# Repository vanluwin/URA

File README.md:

# URA
# Projeto um Robô Por Aluno

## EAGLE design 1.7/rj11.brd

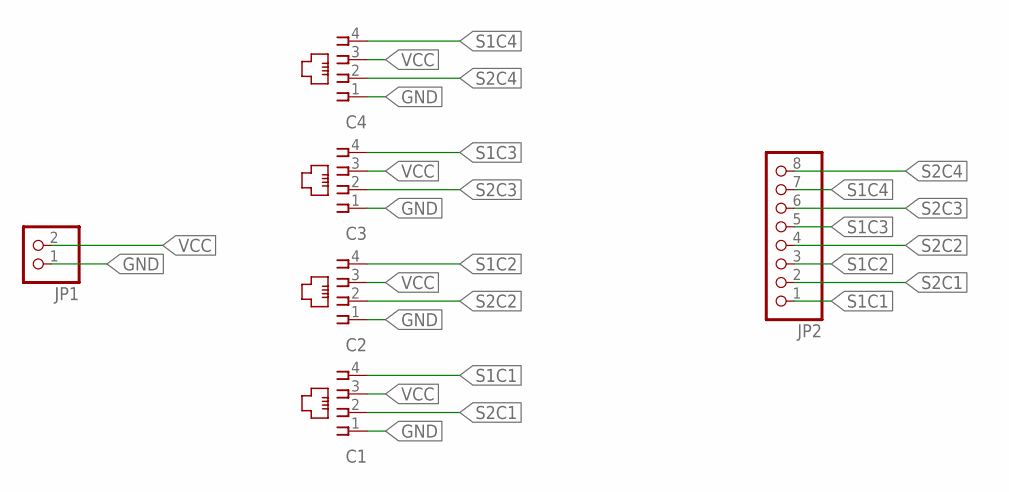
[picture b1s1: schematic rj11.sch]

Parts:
C1, C2, C3, C4: 14867
JP1: PINHD-1X2; 1X02
JP2: PINHD-1X8; 1X08

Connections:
GND: C1.1, C2.1, C3.1, C4.1, JP1.1
S1C1: C1.4, JP2.1
S1C2: C2.4, JP2.3
S1C3: C3.4, JP2.5
S1C4: C4.4, JP2.7
S2C1: C1.2, JP2.2
S2C2: C2.2, JP2.4
S2C3: C3.2, JP2.6
S2C4: C4.2, JP2.8
VCC: C1.3, C2.3, C3.3, C4.3, JP1.2

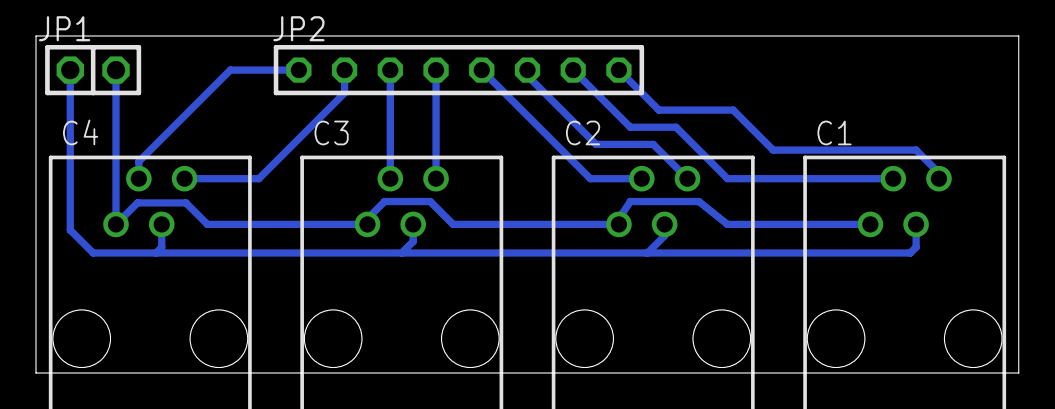
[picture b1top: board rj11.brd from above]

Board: 2 copper layers, 54.6 x 18.7 mm, 6 parts (0 on the bottom side), 10 nets.

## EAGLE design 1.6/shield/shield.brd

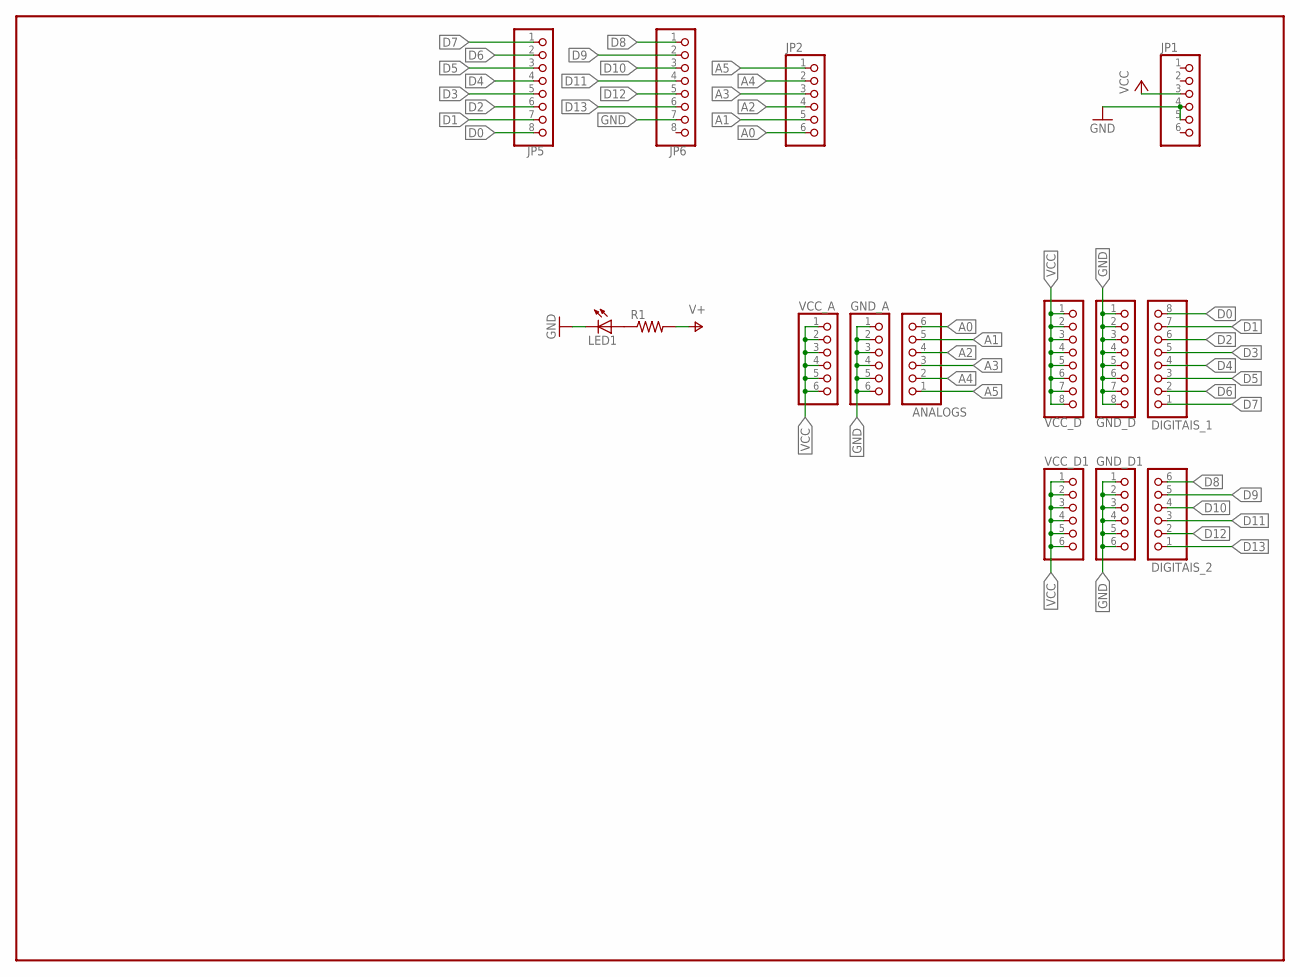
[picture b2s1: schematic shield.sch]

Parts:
ANALOGS: PINHD-1X6; 1X06
DIGITAIS_1: PINHD-1X8; 1X08
DIGITAIS_2: PINHD-1X6; 1X06
GND_A: PINHD-1X6; 1X06
GND_D: PINHD-1X8; 1X08
GND_D1: PINHD-1X6; 1X06
JP1, JP2: PINHD-1X6; 1X06
JP5, JP6: PINHD-1X8; 1X08
LED1: LED3MM
R1: R-US_0207/10; 0207/10
VCC_A: PINHD-1X6; 1X06
VCC_D: PINHD-1X8; 1X08
VCC_D1: PINHD-1X6; 1X06

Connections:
A0: ANALOGS.6, JP2.6
A1: ANALOGS.5, JP2.5
A2: ANALOGS.4, JP2.4
A3: ANALOGS.3, JP2.3
A4: ANALOGS.2, JP2.2
A5: ANALOGS.1, JP2.1
D0: DIGITAIS_1.8, JP5.8
D1: DIGITAIS_1.7, JP5.7
D2: DIGITAIS_1.6, JP5.6
D3: DIGITAIS_1.5, JP5.5
D4: DIGITAIS_1.4, JP5.4
D5: DIGITAIS_1.3, JP5.3
D6: DIGITAIS_1.2, JP5.2
D7: DIGITAIS_1.1, JP5.1
D8: DIGITAIS_2.6, JP6.1
D9: DIGITAIS_2.5, JP6.2
D10: DIGITAIS_2.4, JP6.3
D11: DIGITAIS_2.3, JP6.4
D12: DIGITAIS_2.2, JP6.5
D13: DIGITAIS_2.1, JP6.6
GND: GND_A.1, GND_A.2, GND_A.3, GND_A.4, GND_A.5, GND_A.6, GND_D.1, GND_D.2, GND_D.3, GND_D.4, GND_D.5, GND_D.6, GND_D.7, GND_D.8, GND_D1.1, GND_D1.2, GND_D1.3, GND_D1.4, GND_D1.5, GND_D1.6, JP1.4, JP1.5, JP6.7, LED1.K (C)
unnamed: LED1.A, R1.1
VCC: JP1.3, R1.2, VCC_A.1, VCC_A.2, VCC_A.3, VCC_A.4, VCC_A.5, VCC_A.6, VCC_D.1, VCC_D.2, VCC_D.3, VCC_D.4, VCC_D.5, VCC_D.6, VCC_D.7, VCC_D.8, VCC_D1.1, VCC_D1.2, VCC_D1.3, VCC_D1.4, VCC_D1.5, VCC_D1.6

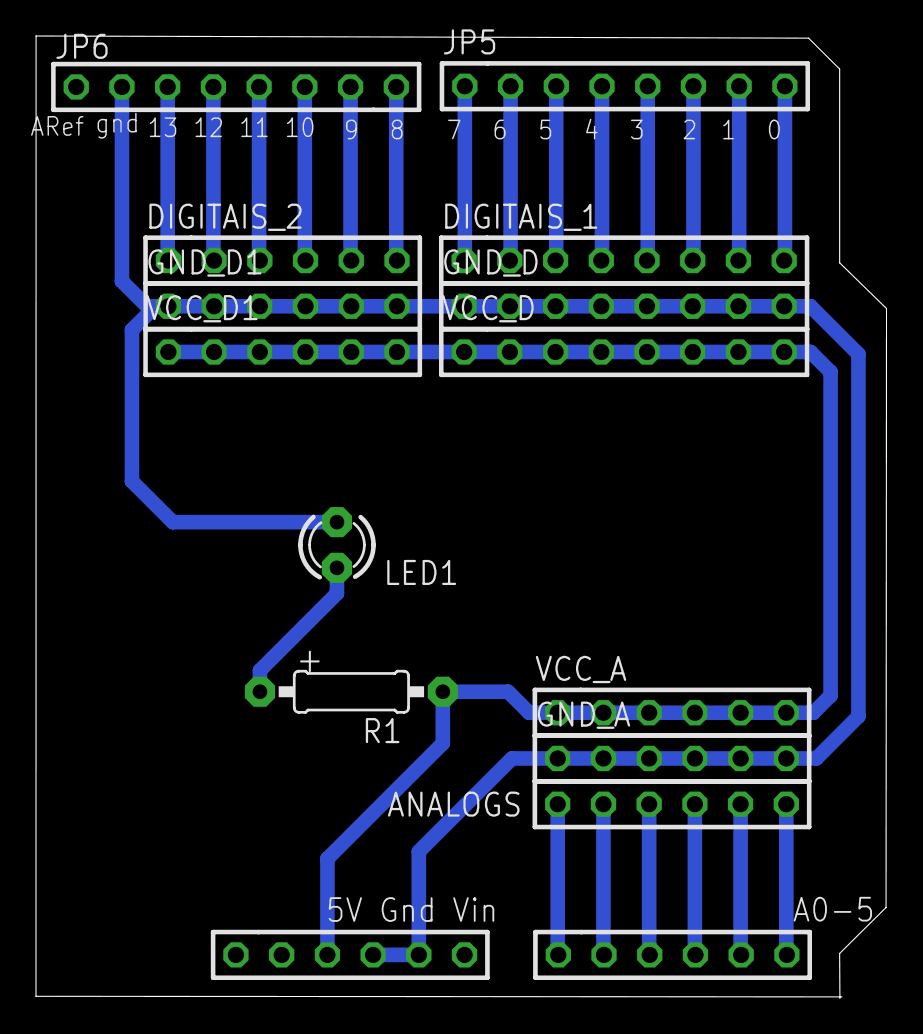
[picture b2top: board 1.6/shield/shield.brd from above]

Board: 2 copper layers, 47.3 x 53.5 mm, 15 parts (0 on the bottom side), 23 nets.

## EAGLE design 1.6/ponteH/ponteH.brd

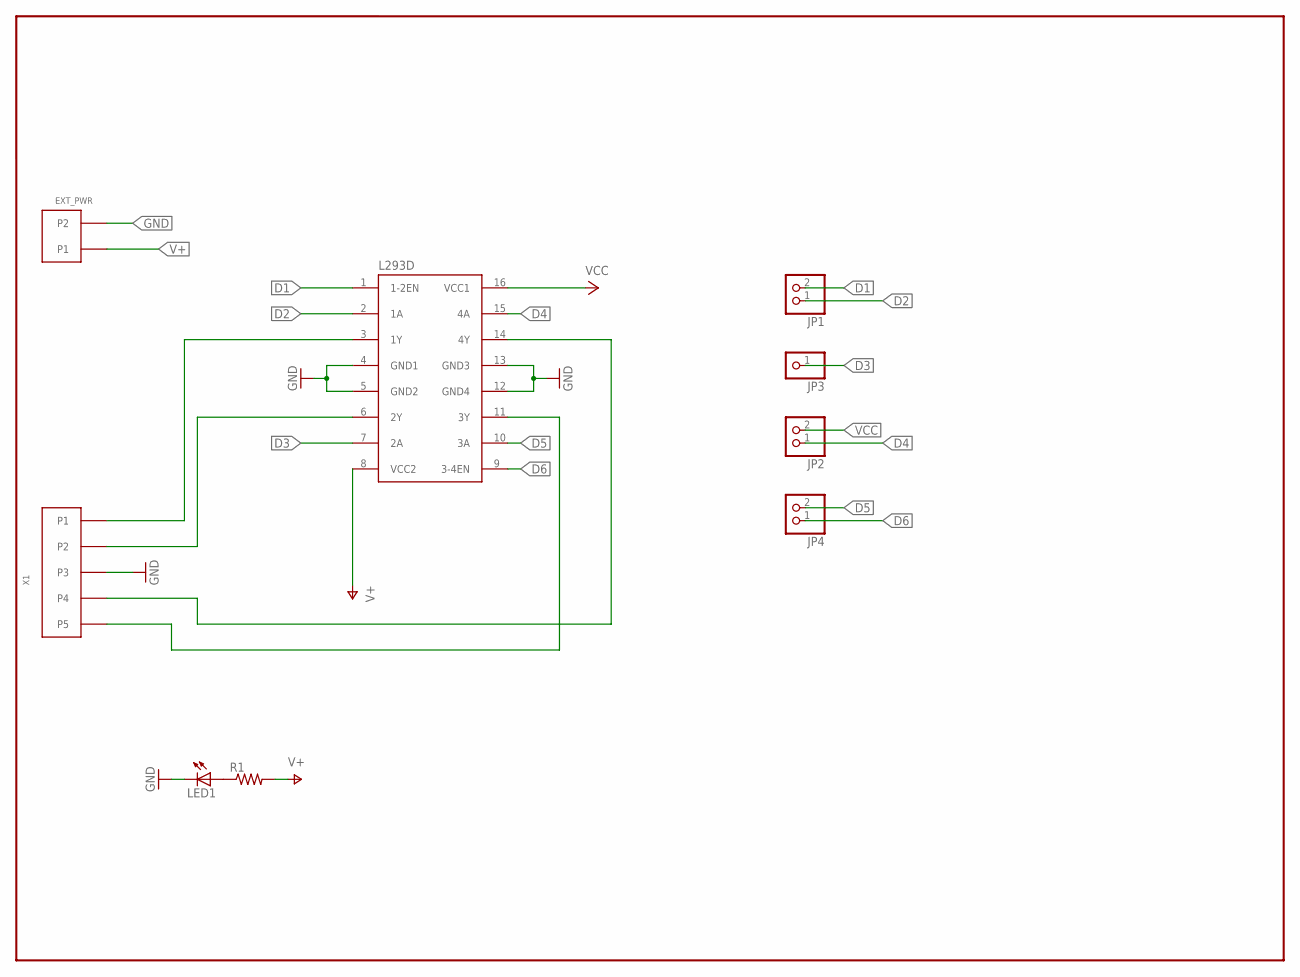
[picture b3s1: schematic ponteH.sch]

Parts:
EXT_PWR: PINHEAD; TERMBLOCK508
JP1, JP2, JP4: PINHD-1X2; 1X02
JP3: PINHD-1X1; 1X01
L293D: L293E; DIL16
LED1: LED3MM
R1: R-US_0207/10; 0207/10
X1: TERM5; TERM1X5

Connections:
D1: JP1.2, L293D.1 (1-2EN)
D2: JP1.1, L293D.2 (1A)
D3: JP3.1, L293D.7 (2A)
D4: JP2.1, L293D.15 (4A)
D5: JP4.2, L293D.10 (3A)
D6: JP4.1, L293D.9 (3-4EN)
GND: EXT_PWR.P$4 (P2), L293D.4 (GND1), L293D.5 (GND2), L293D.12 (GND4), L293D.13 (GND3), LED1.K (C), X1.P3
unnamed: L293D.3 (1Y), X1.P1
unnamed: L293D.6 (2Y), X1.P2
unnamed: L293D.11 (3Y), X1.P5
unnamed: L293D.14 (4Y), X1.P4
unnamed: LED1.A, R1.1
V+: EXT_PWR.P$3 (P1), L293D.8 (VCC2), R1.2
VCC: JP2.2, L293D.16 (VCC1)

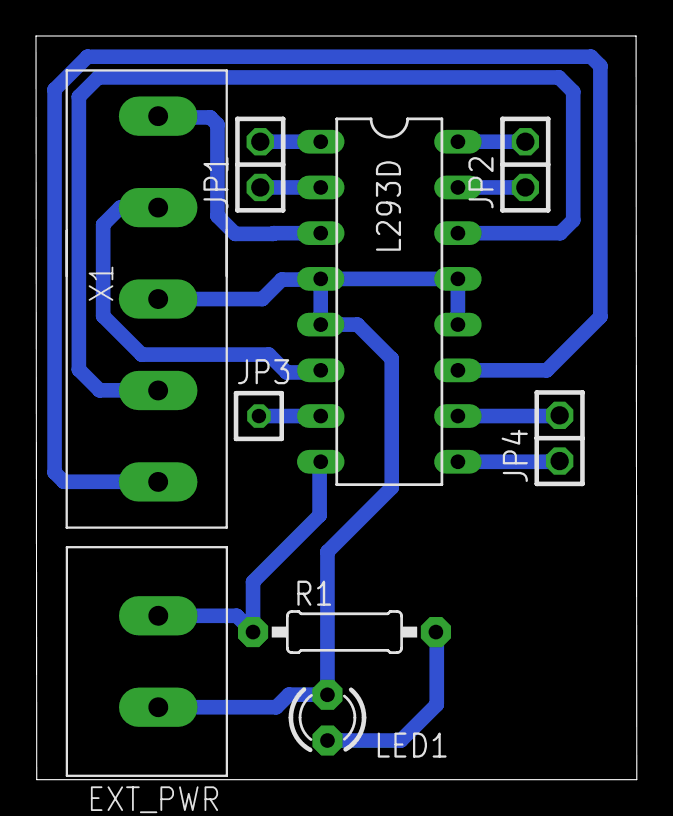
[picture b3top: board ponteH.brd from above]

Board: 2 copper layers, 33.4 x 41.3 mm, 9 parts (0 on the bottom side), 14 nets.

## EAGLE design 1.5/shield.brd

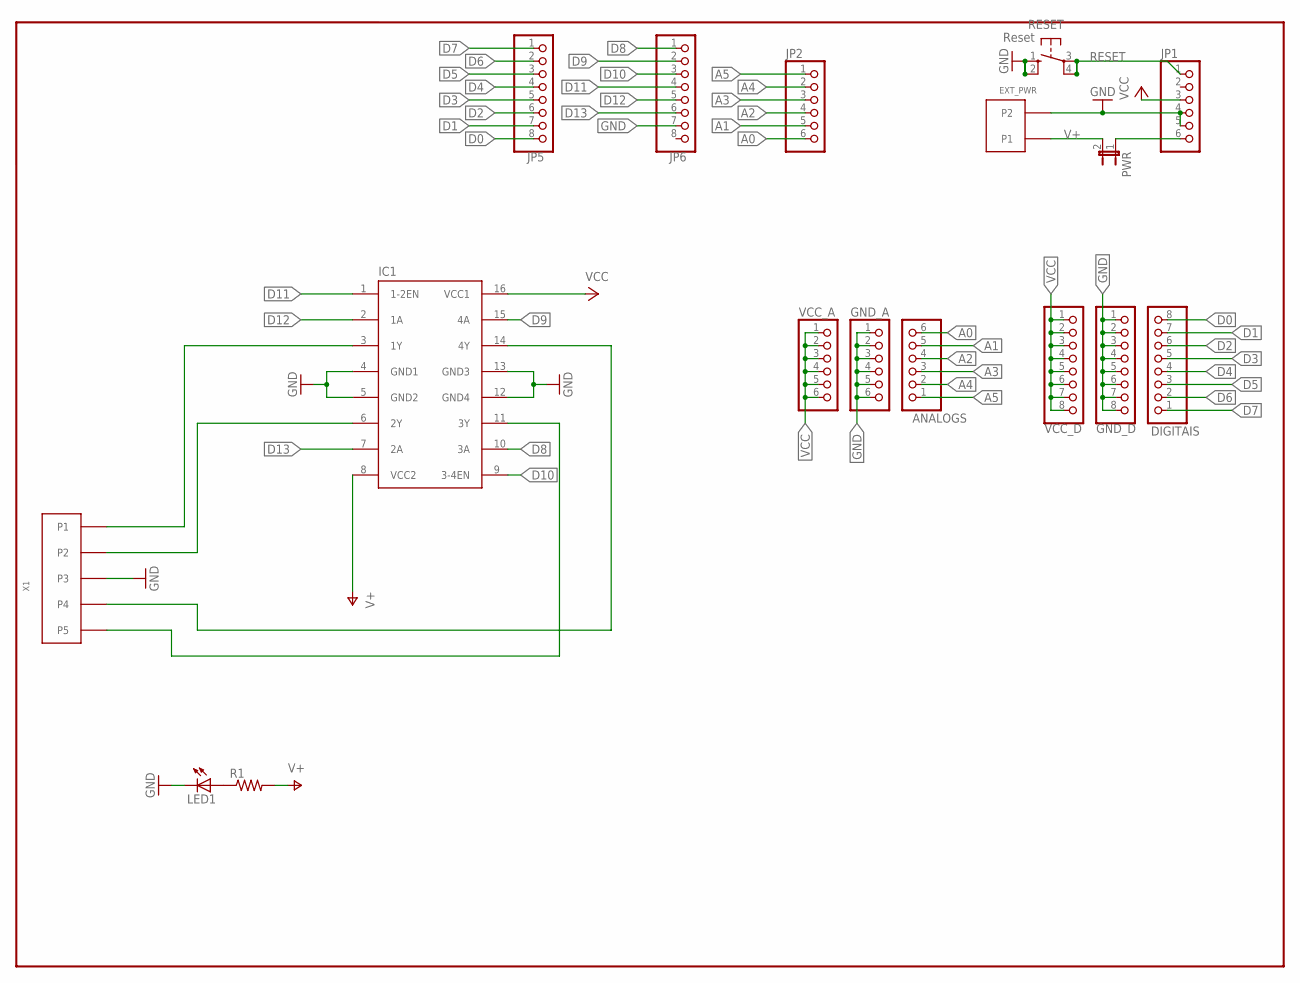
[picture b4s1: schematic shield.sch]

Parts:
ANALOGS: PINHD-1X6; 1X06
DIGITAIS: PINHD-1X8; 1X08
EXT_PWR: PINHEAD; TERMBLOCK508
GND_A: PINHD-1X6; 1X06
GND_D: PINHD-1X8; 1X08
IC1: L293E; DIL16
JP1, JP2: PINHD-1X6; 1X06
JP5, JP6: PINHD-1X8; 1X08
LED1: LED3MM
PWR: JP1E; JP1
R1: R-US_0207/10; 0207/10
RESET: Reset; B3F-10XX
VCC_A: PINHD-1X6; 1X06
VCC_D: PINHD-1X8; 1X08
X1: TERM5; TERM1X5

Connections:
9V: JP1.6, PWR.1
A0: ANALOGS.6, JP2.6
A1: ANALOGS.5, JP2.5
A2: ANALOGS.4, JP2.4
A3: ANALOGS.3, JP2.3
A4: ANALOGS.2, JP2.2
A5: ANALOGS.1, JP2.1
D0: DIGITAIS.8, JP5.8
D1: DIGITAIS.7, JP5.7
D2: DIGITAIS.6, JP5.6
D3: DIGITAIS.5, JP5.5
D4: DIGITAIS.4, JP5.4
D5: DIGITAIS.3, JP5.3
D6: DIGITAIS.2, JP5.2
D7: DIGITAIS.1, JP5.1
D8: IC1.10 (3A), JP6.1
D9: IC1.15 (4A), JP6.2
D10: IC1.9 (3-4EN), JP6.3
D11: IC1.1 (1-2EN), JP6.4
D12: IC1.2 (1A), JP6.5
D13: IC1.7 (2A), JP6.6
GND: EXT_PWR.P$4 (P2), GND_A.1, GND_A.2, GND_A.3, GND_A.4, GND_A.5, GND_A.6, GND_D.1, GND_D.2, GND_D.3, GND_D.4, GND_D.5, GND_D.6, GND_D.7, GND_D.8, IC1.4 (GND1), IC1.5 (GND2), IC1.12 (GND4), IC1.13 (GND3), JP1.4, JP1.5, JP6.7, LED1.K (C), RESET.1 (S), RESET.2 (S1), X1.P3
unnamed: IC1.3 (1Y), X1.P1
unnamed: IC1.6 (2Y), X1.P2
unnamed: IC1.11 (3Y), X1.P5
unnamed: IC1.14 (4Y), X1.P4
unnamed: LED1.A, R1.1
RESET: JP1.1, RESET.3, RESET.4 (P1)
V+: EXT_PWR.P$3 (P1), IC1.8 (VCC2), PWR.2, R1.2
VCC: IC1.16 (VCC1), JP1.3, VCC_A.1, VCC_A.2, VCC_A.3, VCC_A.4, VCC_A.5, VCC_A.6, VCC_D.1, VCC_D.2, VCC_D.3, VCC_D.4, VCC_D.5, VCC_D.6, VCC_D.7, VCC_D.8

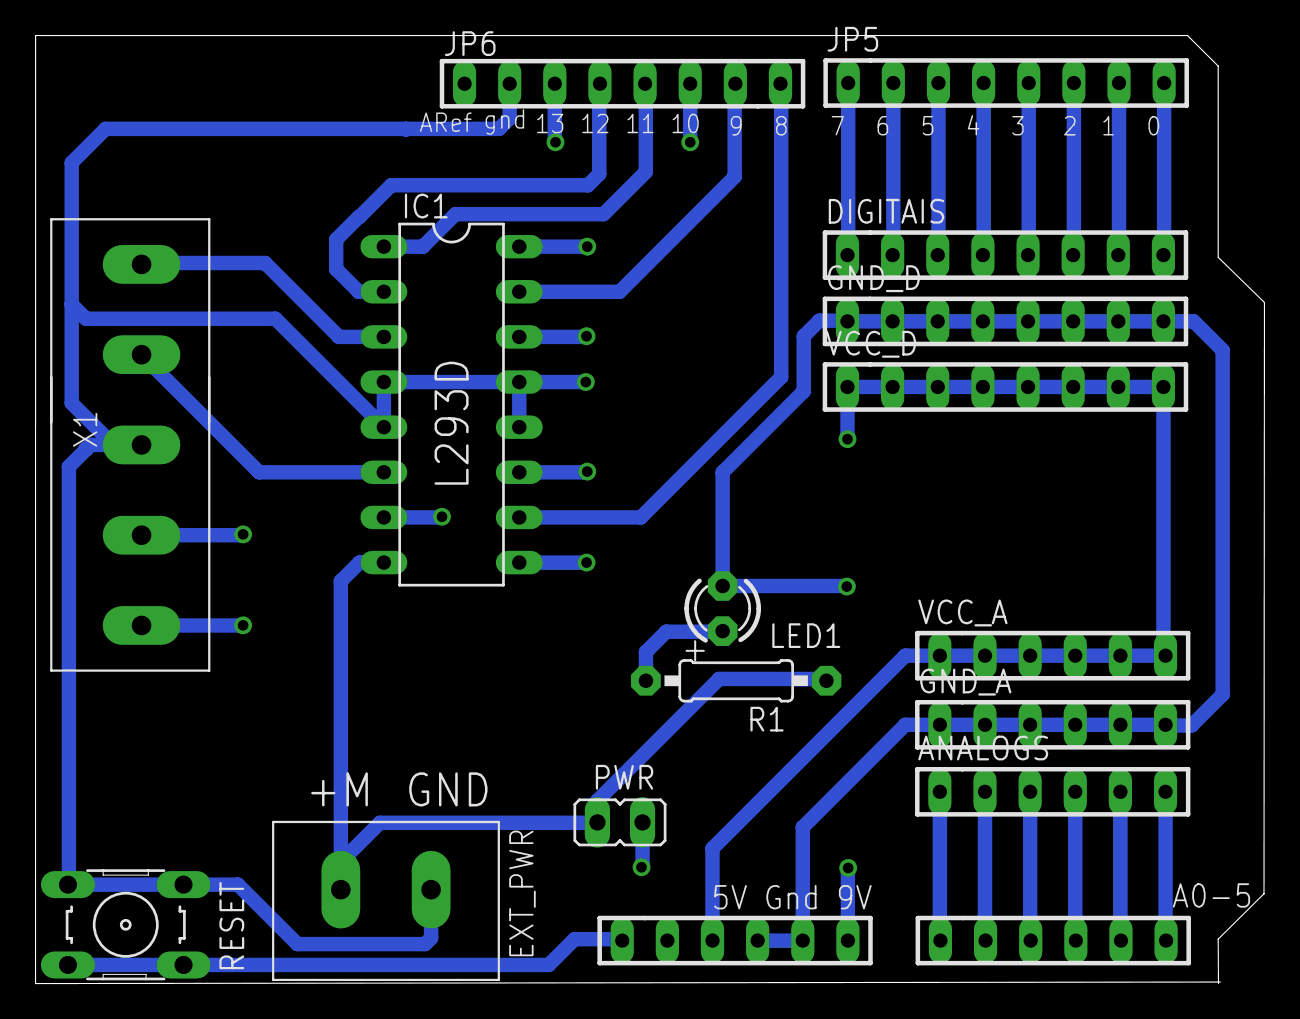
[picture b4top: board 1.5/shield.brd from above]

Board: 2 copper layers, 69.2 x 53.4 mm, 17 parts (0 on the bottom side), 30 nets.

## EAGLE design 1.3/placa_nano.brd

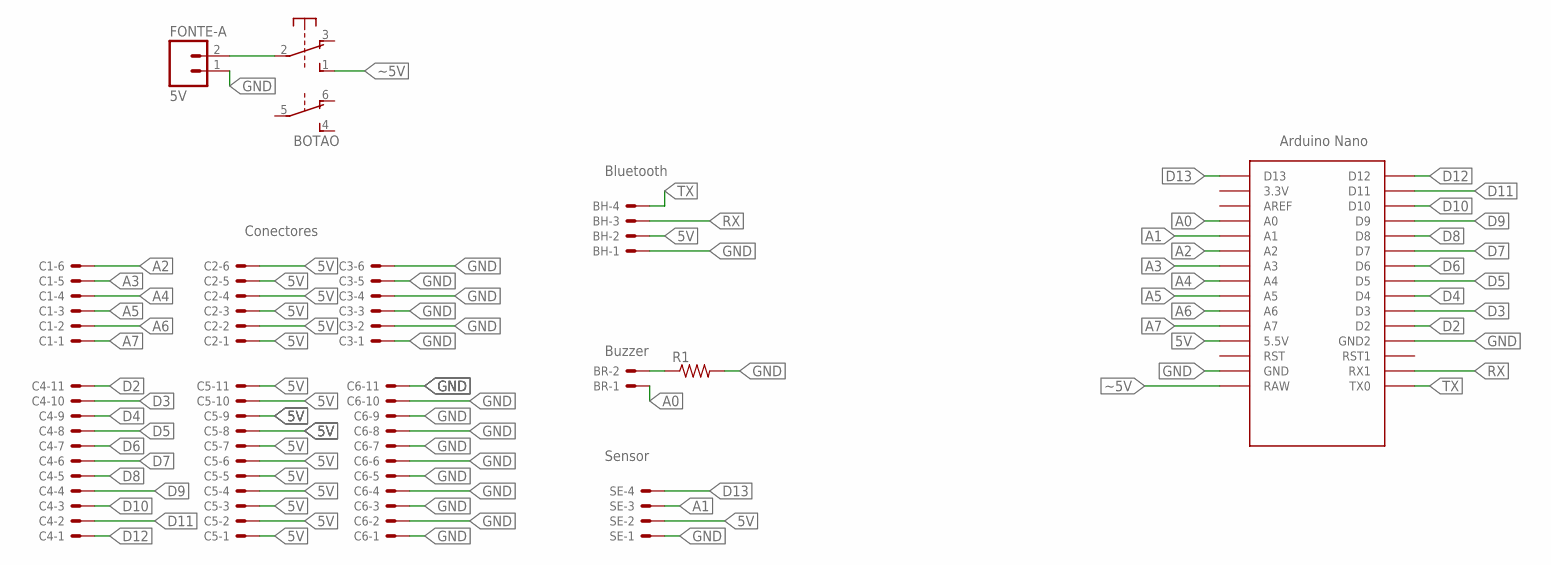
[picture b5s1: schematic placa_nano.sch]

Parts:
BH: 22-23-2041
BOTAO: 9077-2
BR: 22-23-2021
C1, C2, C3: 22-23-2061
C4, C5, C6: 22-23-2111
FONTE-A: 5V; 02P
R1: R-US_0207/10; 0207/10
SE: 22-23-2041
U$1: NANO

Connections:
5V: BH.2, C2.1, C2.2, C2.3, C2.4, C2.5, C2.6, C5.1, C5.2, C5.3, C5.4, C5.5, C5.6, C5.7, C5.8, C5.9, C5.10, C5.11, SE.2, U$1.5V (5.5V)
A0: BR.1, U$1.A0
A1: SE.3, U$1.A1
A2: C1.6, U$1.A2
A3: C1.5, U$1.A3
A4: C1.4, U$1.A4
A5: C1.3, U$1.A5
A6: C1.2, U$1.A6
A7: C1.1, U$1.A7
D2: C4.11, U$1.D2
D3: C4.10, U$1.D3
D4: C4.9, U$1.D4
D5: C4.8, U$1.D5
D6: C4.7, U$1.D6
D7: C4.6, U$1.D7
D8: C4.5, U$1.D8
D9: C4.4, U$1.D9
D10: C4.3, U$1.D10
D11: C4.2, U$1.D11
D12: C4.1, U$1.D12
D13: SE.4, U$1.D13
GND: BH.1, C3.1, C3.2, C3.3, C3.4, C3.5, C3.6, C6.1, C6.2, C6.3, C6.4, C6.5, C6.6, C6.7, C6.8, C6.9, C6.10, C6.11, FONTE-A.1, R1.2, SE.1, U$1.GND, U$1.GND1 (GND2)
unnamed: BR.2, R1.1
RX: BH.3, U$1.RX1
TX: BH.4, U$1.TX0
~5V: BOTAO.1 (S), BOTAO.2, FONTE-A.2, U$1.RAW

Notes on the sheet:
Bluetooth
Buzzer
Sensor
Conectores

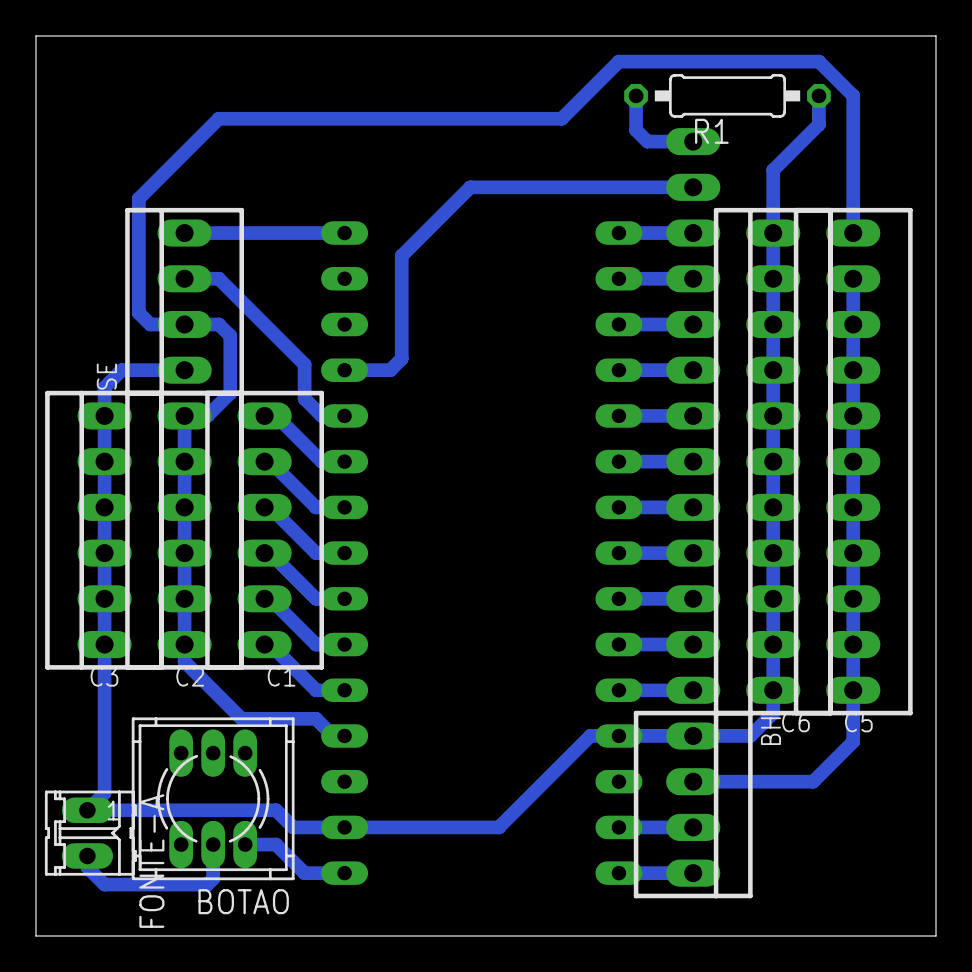
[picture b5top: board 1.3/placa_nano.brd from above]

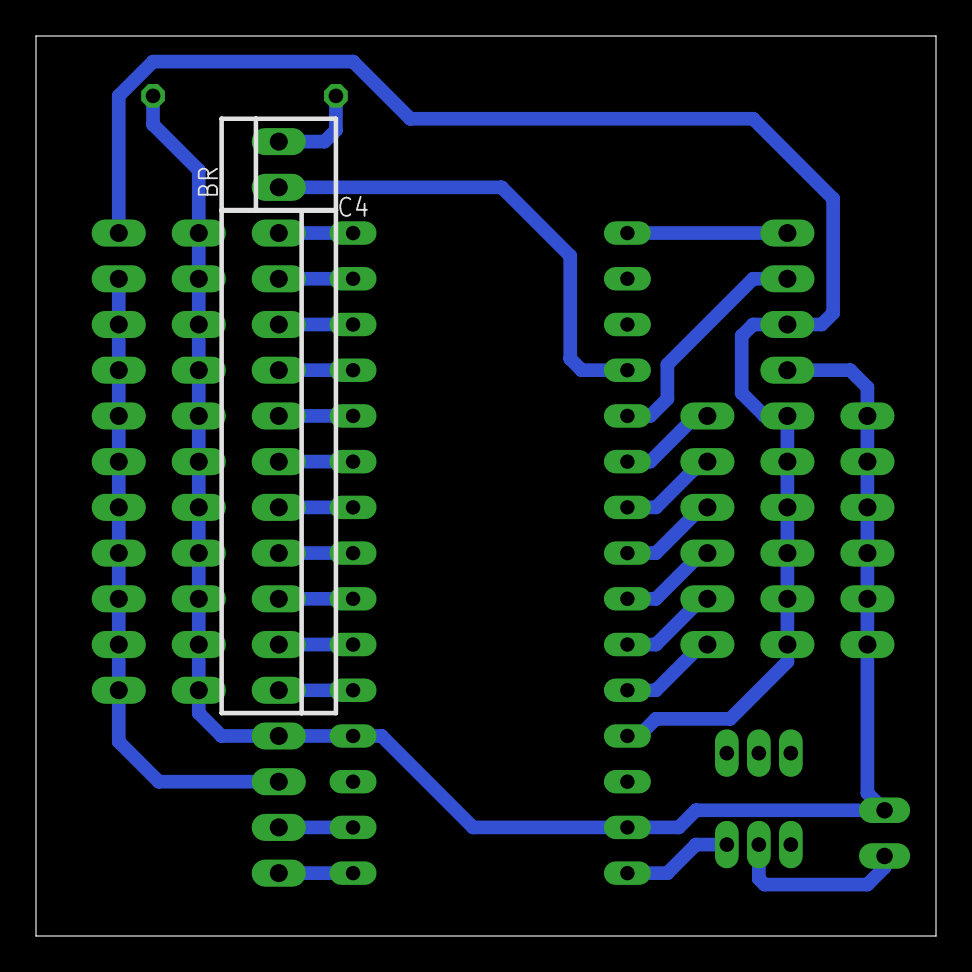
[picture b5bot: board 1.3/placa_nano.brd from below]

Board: 2 copper layers, 50.0 x 50.0 mm, 13 parts (2 on the bottom side), 26 nets.

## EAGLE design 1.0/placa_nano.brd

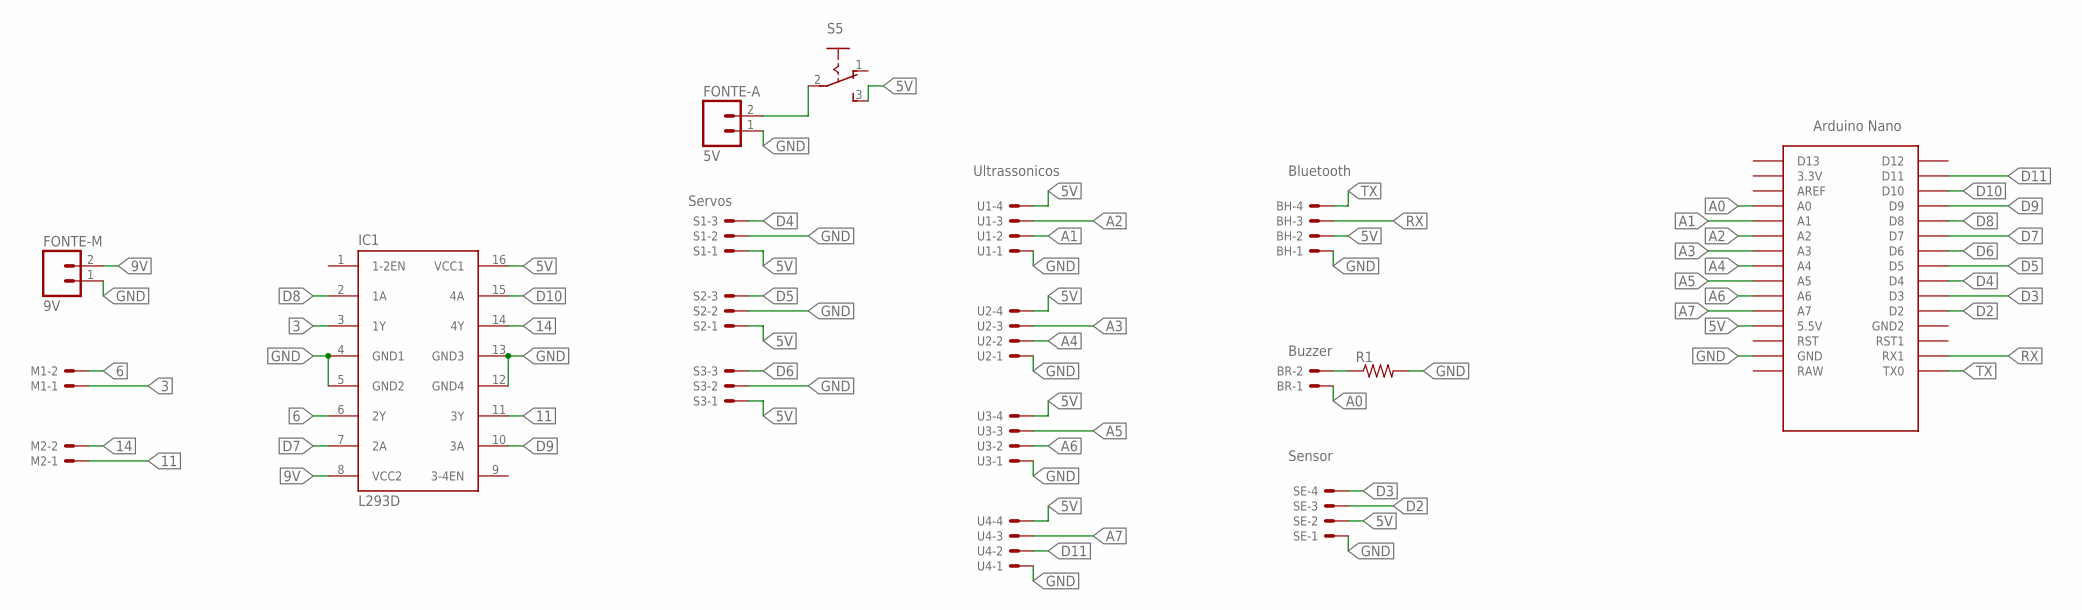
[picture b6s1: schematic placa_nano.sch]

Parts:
BH: 22-23-2041
BR: 22-23-2021
FONTE-A: 5V; 02P
FONTE-M: 9V; 02P
IC1: L293D; DIL16
M1, M2: 22-23-2021
R1: R-US_0207/10; 0207/10
S1, S2, S3: 22-23-2031
S5: 255SB
SE: 22-23-2041
U1, U2, U3, U4: 22-23-2041
U$1: NANO

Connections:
3: IC1.3 (1Y), M1.1
5V: BH.2, FONTE-A.2, IC1.16 (VCC1), S1.1, S2.1, S3.1, S5.2, S5.3 (S), SE.2, U1.4, U2.4, U3.4, U4.4, U$1.5V (5.5V)
6: IC1.6 (2Y), M1.2
9V: FONTE-M.2, IC1.8 (VCC2)
11: IC1.11 (3Y), M2.1
14: IC1.14 (4Y), M2.2
A0: BR.1, U$1.A0
A1: U1.2, U$1.A1
A2: U1.3, U$1.A2
A3: U2.3, U$1.A3
A4: U2.2, U$1.A4
A5: U3.3, U$1.A5
A6: U3.2, U$1.A6
A7: U4.3, U$1.A7
D2: SE.3, U$1.D2
D3: SE.4, U$1.D3
D4: S1.3, U$1.D4
D5: S2.3, U$1.D5
D6: S3.3, U$1.D6
D7: IC1.7 (2A), U$1.D7
D8: IC1.2 (1A), U$1.D8
D9: IC1.10 (3A), U$1.D9
D10: IC1.15 (4A), U$1.D10
D11: U4.2, U$1.D11
GND: BH.1, FONTE-A.1, FONTE-M.1, IC1.4 (GND1), IC1.5 (GND2), IC1.12 (GND4), IC1.13 (GND3), R1.2, S1.2, S2.2, S3.2, SE.1, U1.1, U2.1, U3.1, U4.1, U$1.GND
unnamed: BR.2, R1.1
RX: BH.3, U$1.RX1
TX: BH.4, U$1.TX0

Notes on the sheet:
Servos
Ultrassonicos
Bluetooth
Buzzer
Sensor

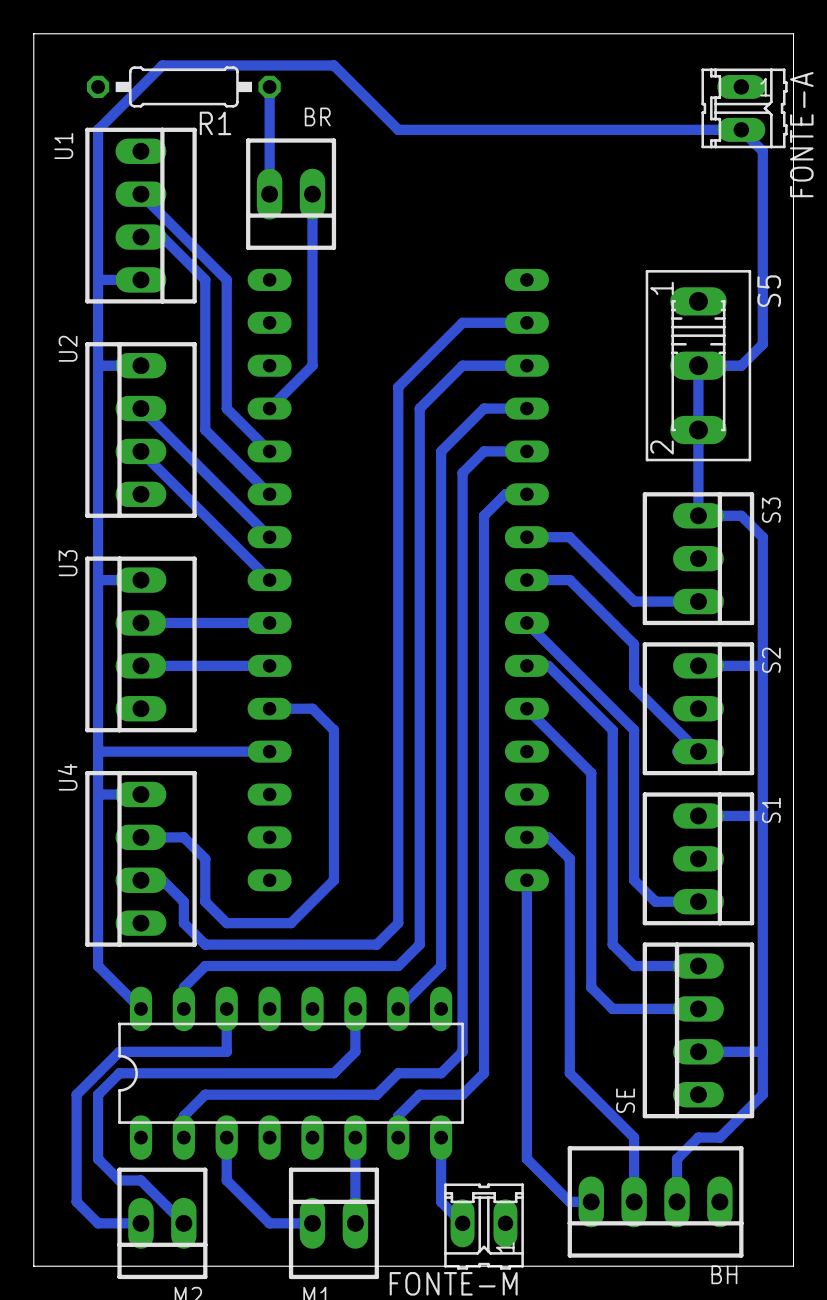
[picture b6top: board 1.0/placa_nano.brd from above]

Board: 2 copper layers, 45.0 x 73.0 mm, 18 parts (0 on the bottom side), 28 nets.

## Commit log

2017-05-15 Arquivos das Plcas
2017-05-19 Placa do projeto URA para seguidor de linha
2017-05-31 Nova versão da placa
2017-06-09 shield arduino uno para laboratório de robótica
2017-06-17 Shield para arduino uno, com ponte H para controle de motores DC.
2017-08-02 Circuito para a ponte H
2017-08-02 Shield com ampliação dos conectores
2017-08-24 Placa com o conector RJ11
